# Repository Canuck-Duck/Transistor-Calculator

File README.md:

# Transistor-Calculator

V0.1 has many problems with the schematic and the PCB design. First, the schematic contains a mistake with both XOR segments. A wire is supposed to go from the right resistor under Q10 to 5V and from the right resistor under Q14 to 5V. Also, the design of the PCB is flawed because it is hard to hand-solder. While designing this PCB, I was too focused on saving space, which should not have been the case for the first version. The input and output holes were too small to fit any regular-size wire. All of these problems were fixed in V0.3.

V0.3 fixed all of the problems mentioned but still has some. For example, there are no mounting holes, so I had to drill holes in the PBC for the standoffs to stack them. Also, the 5V and GND will run through the standoffs for the following versions to facilitate disassembly. The carry pins will also be on the same side as the input since that's where it has to connect.

The 7-segment display module V1 translates an 8-bit binary number into an easier-to-read decimal number. This module can be connected anywhere in the calculator where the user wants to read the value of an 8-bit binary number. It uses two programmed EEPROMs to translate the 8-bit binary into 3 BCD, which are fed into 7-segment display drivers to convert the BCD for the 7-segment display (common anode).

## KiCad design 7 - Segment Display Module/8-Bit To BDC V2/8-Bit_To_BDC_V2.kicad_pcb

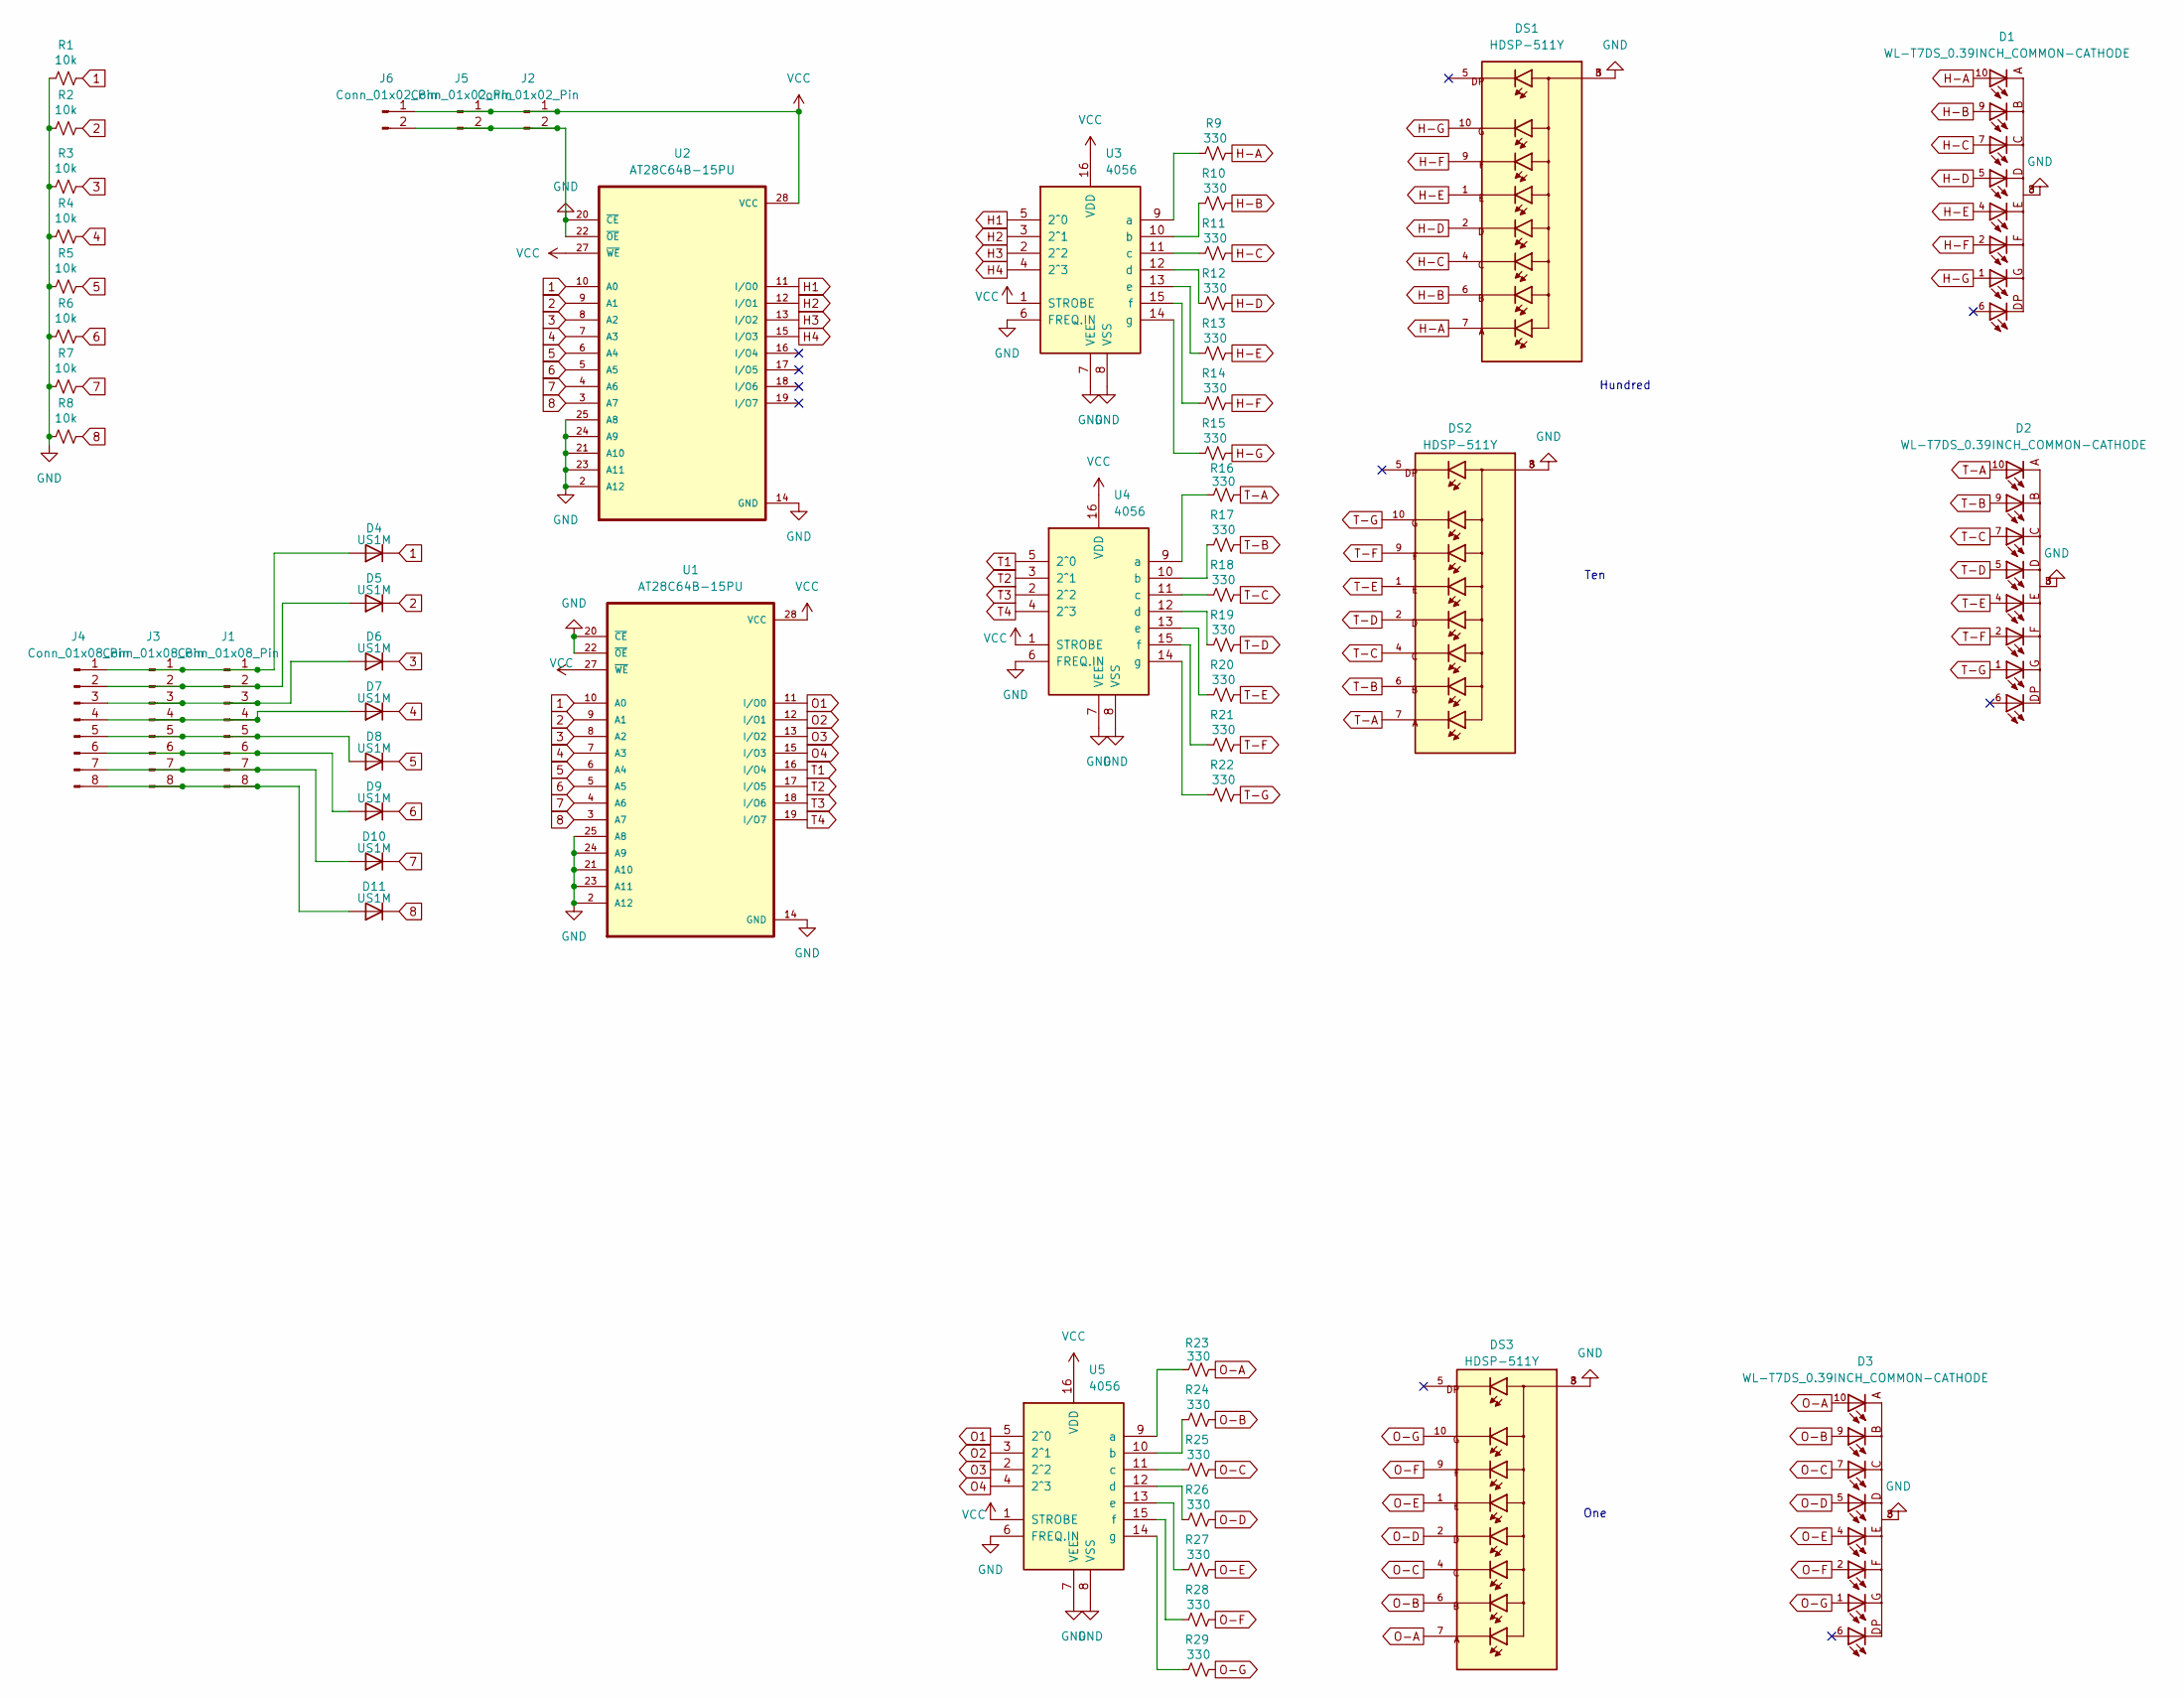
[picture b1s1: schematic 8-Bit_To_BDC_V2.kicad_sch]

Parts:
D1, D2, D3: WL-T7DS_0.39INCH_COMMON-CATHODE; WL-T7DS_0.39INCH
D4, D5, D6, D7, D8, D9, D10, D11: US1M; D_SOD-323_HandSoldering; LCSC C2128
DS1, DS2, DS3: HDSP-511Y; LED_HDSP-511Y; PARTREV April 12, 2021
J1, J3, J4: Conn_01x08_Pin; PinHeader_2x04_P2.54mm_Vertical
J2, J5, J6: Conn_01x02_Pin; PinHeader_1x02_P2.54mm_Vertical
R1, R2, R3, R4, R5, R6, R7, R8: 10k; C_0402_1005Metric_Pad0.74x0.62mm_HandSolder; LCSC C25744
R9, R10, R11, R12, R13, R14, R15, R16, R17, R18, R19, R20, R21, R22, R23, R24, R25, R26, R27, R28, R29: 330; R_0805_2012Metric_Pad1.20x1.40mm_HandSolder; LCSC C17630
U1, U2: AT28C64B-15PU; DIP1555W45P254L3733H482Q28; PARTREV B
U3, U4, U5: 4056; DIP794W45P254L1969H508Q16

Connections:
1: D4.1 (K), R1.2, U1.10 (A0), U2.10 (A0)
2: D5.1 (K), R2.2, U1.9 (A1), U2.9 (A1)
3: D6.1 (K), R3.2, U1.8 (A2), U2.8 (A2)
4: D7.1 (K), R4.2, U1.7 (A3), U2.7 (A3)
5: D8.1 (K), R5.2, U1.6 (A4), U2.6 (A4)
6: D9.1 (K), R6.2, U1.5 (A5), U2.5 (A5)
7: D10.1 (K), R7.2, U1.4 (A6), U2.4 (A6)
8: D11.1 (K), R8.2, U1.3 (A7), U2.3 (A7)
GND: D1.3, D1.8, D2.3, D2.8, D3.3, D3.8, DS1.3, DS1.8, DS2.3, DS2.8, DS3.3, DS3.8, J2.2, J5.2, J6.2, R1.1, R2.1, R3.1, R4.1, R5.1, R6.1, R7.1, R8.1, U1.2 (A12), U1.14 (GND), U1.20 (~CE), U1.21 (A10), U1.22 (~OE), U1.23 (A11), U1.24 (A9), U1.25 (A8), U2.2 (A12), U2.14 (GND), U2.20 (~CE), U2.21 (A10), U2.22 (~OE), U2.23 (A11), U2.24 (A9), U2.25 (A8), U3.6 (FREQ.IN), U3.7 (VEE), U3.8 (VSS), U4.6 (FREQ.IN), U4.7 (VEE), U4.8 (VSS), U5.6 (FREQ.IN), U5.7 (VEE), U5.8 (VSS)
H1: U2.11 (I/O0), U3.5 (2^0)
H2: U2.12 (I/O1), U3.3 (2^1)
H3: U2.13 (I/O2), U3.2 (2^2)
H4: U2.15 (I/O3), U3.4 (2^3)
H-A: D1.10, DS1.7, R9.2
H-B: D1.9, DS1.6, R10.2
H-C: D1.7, DS1.4, R11.2
H-D: D1.5, DS1.2, R12.2
H-E: D1.4, DS1.1, R13.2
H-F: D1.2, DS1.9, R14.2
H-G: D1.1, DS1.10, R15.2
unnamed: D4.2 (A), J1.1, J3.1, J4.1
unnamed: D5.2 (A), J1.2, J3.2, J4.2
unnamed: D6.2 (A), J1.3, J3.3, J4.3
unnamed: D7.2 (A), J1.4, J3.4, J4.4
unnamed: D8.2 (A), J1.5, J3.5, J4.5
unnamed: D9.2 (A), J1.6, J3.6, J4.6
unnamed: D10.2 (A), J1.7, J3.7, J4.7
unnamed: D11.2 (A), J1.8, J3.8, J4.8
unnamed: R9.1, U3.9 (a)
unnamed: R10.1, U3.10 (b)
unnamed: R11.1, U3.11 (c)
unnamed: R12.1, U3.12 (d)
unnamed: R13.1, U3.13 (e)
unnamed: R14.1, U3.15 (f)
unnamed: R15.1, U3.14 (g)
unnamed: R16.1, U4.9 (a)
unnamed: R17.1, U4.10 (b)
unnamed: R18.1, U4.11 (c)
unnamed: R19.1, U4.12 (d)
unnamed: R20.1, U4.13 (e)
unnamed: R21.1, U4.15 (f)
unnamed: R22.1, U4.14 (g)
unnamed: R23.1, U5.9 (a)
unnamed: R24.1, U5.10 (b)
unnamed: R25.1, U5.11 (c)
unnamed: R26.1, U5.12 (d)
unnamed: R27.1, U5.13 (e)
unnamed: R28.1, U5.15 (f)
unnamed: R29.1, U5.14 (g)
O1: U1.11 (I/O0), U5.5 (2^0)
O2: U1.12 (I/O1), U5.3 (2^1)
O3: U1.13 (I/O2), U5.2 (2^2)
O4: U1.15 (I/O3), U5.4 (2^3)
O-A: D3.10, DS3.7, R23.2
O-B: D3.9, DS3.6, R24.2
O-C: D3.7, DS3.4, R25.2
O-D: D3.5, DS3.2, R26.2
O-E: D3.4, DS3.1, R27.2
O-F: D3.2, DS3.9, R28.2
O-G: D3.1, DS3.10, R29.2
T1: U1.16 (I/O4), U4.5 (2^0)
T2: U1.17 (I/O5), U4.3 (2^1)
T3: U1.18 (I/O6), U4.2 (2^2)
T4: U1.19 (I/O7), U4.4 (2^3)
T-A: D2.10, DS2.7, R16.2
T-B: D2.9, DS2.6, R17.2
T-C: D2.7, DS2.4, R18.2
T-D: D2.5, DS2.2, R19.2
T-E: D2.4, DS2.1, R20.2
T-F: D2.2, DS2.9, R21.2
T-G: D2.1, DS2.10, R22.2
VCC: J2.1, J5.1, J6.1, U1.27 (~WE), U1.28 (VCC), U2.27 (~WE), U2.28 (VCC), U3.1 (STROBE), U3.16 (VDD), U4.1 (STROBE), U4.16 (VDD), U5.1 (STROBE), U5.16 (VDD)

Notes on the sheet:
Ten
One
Hundred

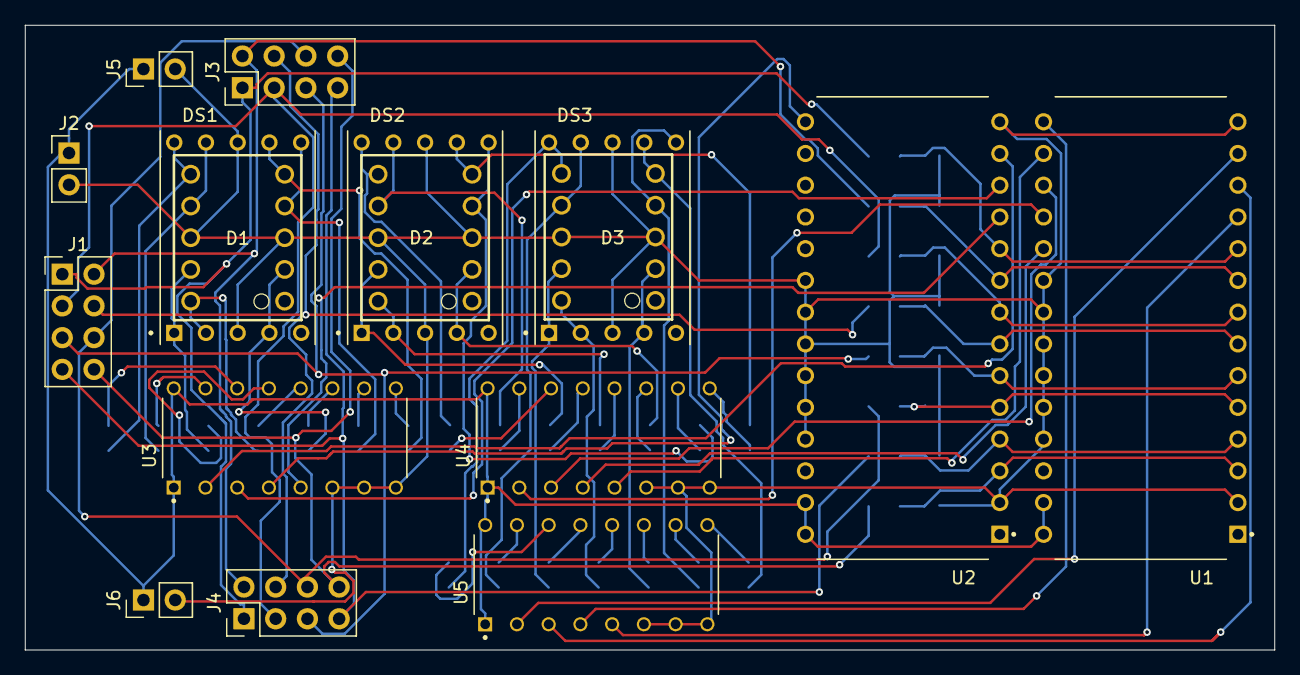
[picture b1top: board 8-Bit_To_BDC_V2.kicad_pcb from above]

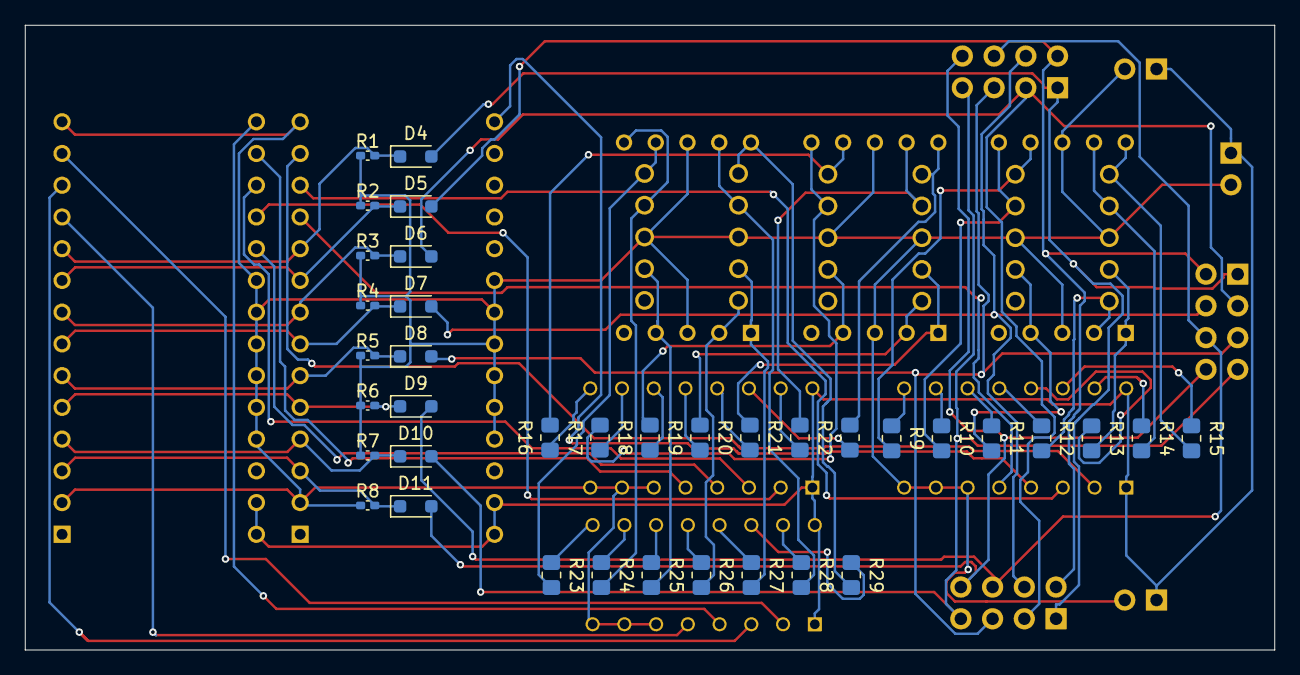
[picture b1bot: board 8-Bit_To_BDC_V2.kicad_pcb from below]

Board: 2 copper layers, 100.0 x 50.0 mm, 54 parts (37 on the bottom side), 72 nets.

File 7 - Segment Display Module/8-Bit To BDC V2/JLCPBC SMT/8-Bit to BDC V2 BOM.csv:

"null","Sourced","Placed","References","Value","Footprint","Quantity"
1,"","","R9, R10, R11, R12, R13, R14, R15, R16, R17, R18, R19, R20, R21, R23, R24, R25, R26, R27, R28, R29, R30",330,"R_0805_2012Metric_Pad1.20x1.40mm_HandSolder",21
2,"","","R1, R2, R3, R4, R5, R6, R7, R8","10k","C_0402_1005Metric_Pad0.74x0.62mm_HandSolder",8

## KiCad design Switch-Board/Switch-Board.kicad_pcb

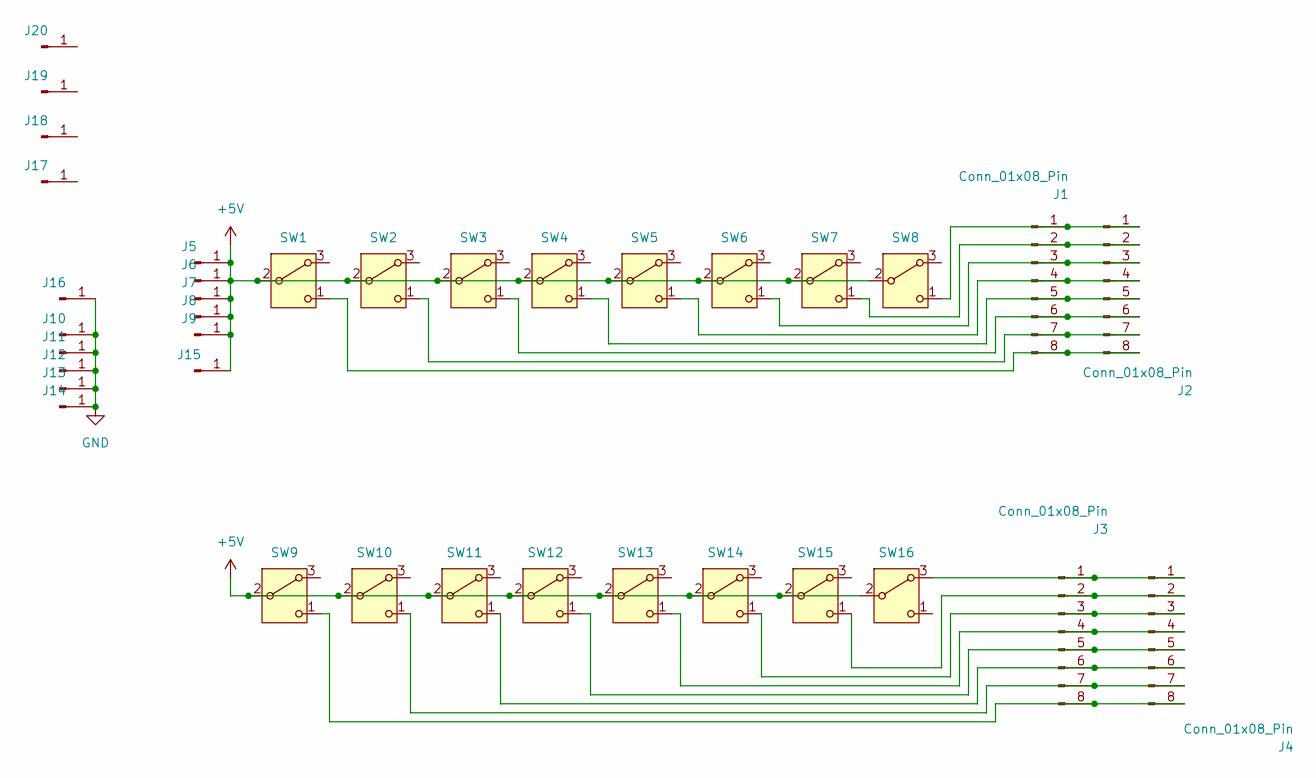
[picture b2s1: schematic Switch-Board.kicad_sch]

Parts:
J1, J3: Conn_01x08_Pin; PinSocket_2x04_P2.54mm_Vertical
J2, J4: Conn_01x08_Pin; PinHeader_1x08_P2.54mm_Vertical
J5, J6, J7, J8, J9: Conn_01x01_Pin; Pin_D1.0mm_L10.0mm_LooseFit
J10, J11, J12, J13, J14: Conn_01x01_Pin; Pin_D1.4mm_L8.5mm_W2.8mm_FlatFork
J15, J16: Conn_01x01_Pin; MountingHole_2.5mm_Pad
J17, J18, J19, J20: Conn_01x01_Pin; MountingHole_3.2mm_M3_DIN965_Pad
SW1, SW2, SW3, SW4, SW5, SW6, SW7, SW8, SW9, SW10, SW11, SW12, SW13, SW14, SW15, SW16: SW_Nidec_CAS-120A1; 5mm_Linear_Switch

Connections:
+5V: J5.1, J6.1, J7.1, J8.1, J9.1, J15.1, SW1.2 (B), SW2.2 (B), SW3.2 (B), SW4.2 (B), SW5.2 (B), SW6.2 (B), SW7.2 (B), SW8.2 (B), SW9.2 (B), SW10.2 (B), SW11.2 (B), SW12.2 (B), SW13.2 (B), SW14.2 (B), SW15.2 (B), SW16.2 (B)
GND: J10.1, J11.1, J12.1, J13.1, J14.1, J16.1
unnamed: J1.1, J2.1, SW8.1 (C)
unnamed: J1.2, J2.2, SW7.1 (C)
unnamed: J1.3, J2.3, SW6.1 (C)
unnamed: J1.4, J2.4, SW5.1 (C)
unnamed: J1.5, J2.5, SW4.1 (C)
unnamed: J1.6, J2.6, SW3.1 (C)
unnamed: J1.7, J2.7, SW2.1 (C)
unnamed: J1.8, J2.8, SW1.1 (C)
unnamed: J3.1, J4.1, SW16.3 (A)
unnamed: J3.2, J4.2, SW15.1 (C)
unnamed: J3.3, J4.3, SW14.1 (C)
unnamed: J3.4, J4.4, SW13.1 (C)
unnamed: J3.5, J4.5, SW12.1 (C)
unnamed: J3.6, J4.6, SW11.1 (C)
unnamed: J3.7, J4.7, SW10.1 (C)
unnamed: J3.8, J4.8, SW9.1 (C)

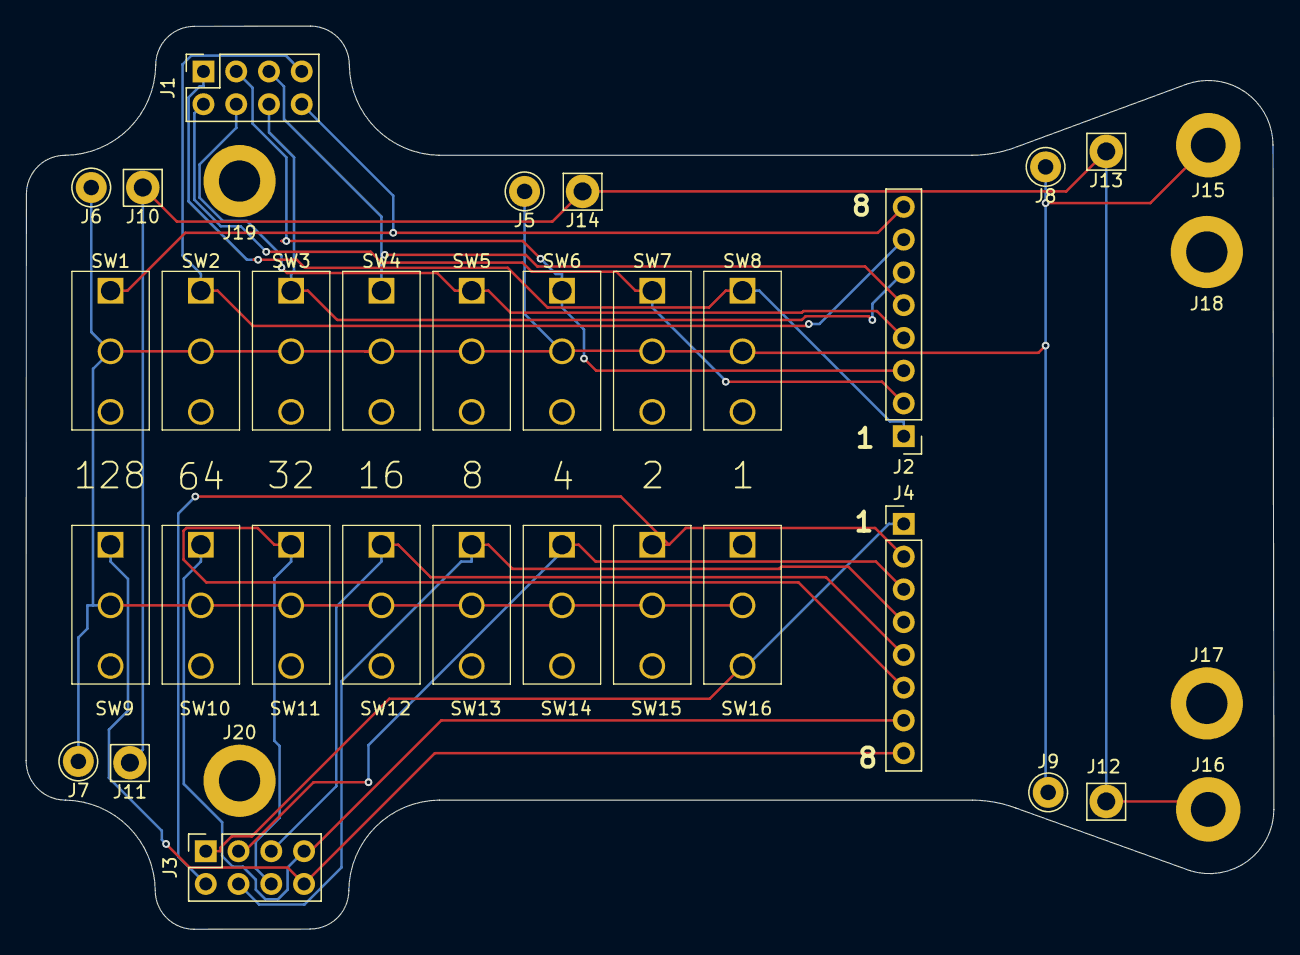
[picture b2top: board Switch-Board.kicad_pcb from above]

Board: 2 copper layers, 96.7 x 70.0 mm, 36 parts (0 on the bottom side), 18 nets.

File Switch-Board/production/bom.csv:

Designator,Footprint,Quantity,Value,LCSC Part #
"J1, J3",PinSocket_2x04_P2.54mm_Vertical,2,Conn_01x08_Pin,
"J10, J11, J12, J13, J14",Pin_D1.4mm_L8.5mm_W2.8mm_FlatFork,5,Conn_01x01_Pin,
"J15, J16",MountingHole_2.5mm_Pad,2,Conn_01x01_Pin,
"J17, J18, J19, J20",MountingHole_3.2mm_M3_DIN965_Pad,4,Conn_01x01_Pin,
"J2, J4",PinHeader_1x08_P2.54mm_Vertical,2,Conn_01x08_Pin,
"J5, J6, J7, J8, J9",Pin_D1.0mm_L10.0mm_LooseFit,5,Conn_01x01_Pin,
"SW1, SW10, SW11, SW12, SW13, SW14, SW15, SW16, SW2, SW3, SW4, SW5, SW6, SW7, SW8, SW9",5mm_Linear_Switch,16,SW_Nidec_CAS-120A1,

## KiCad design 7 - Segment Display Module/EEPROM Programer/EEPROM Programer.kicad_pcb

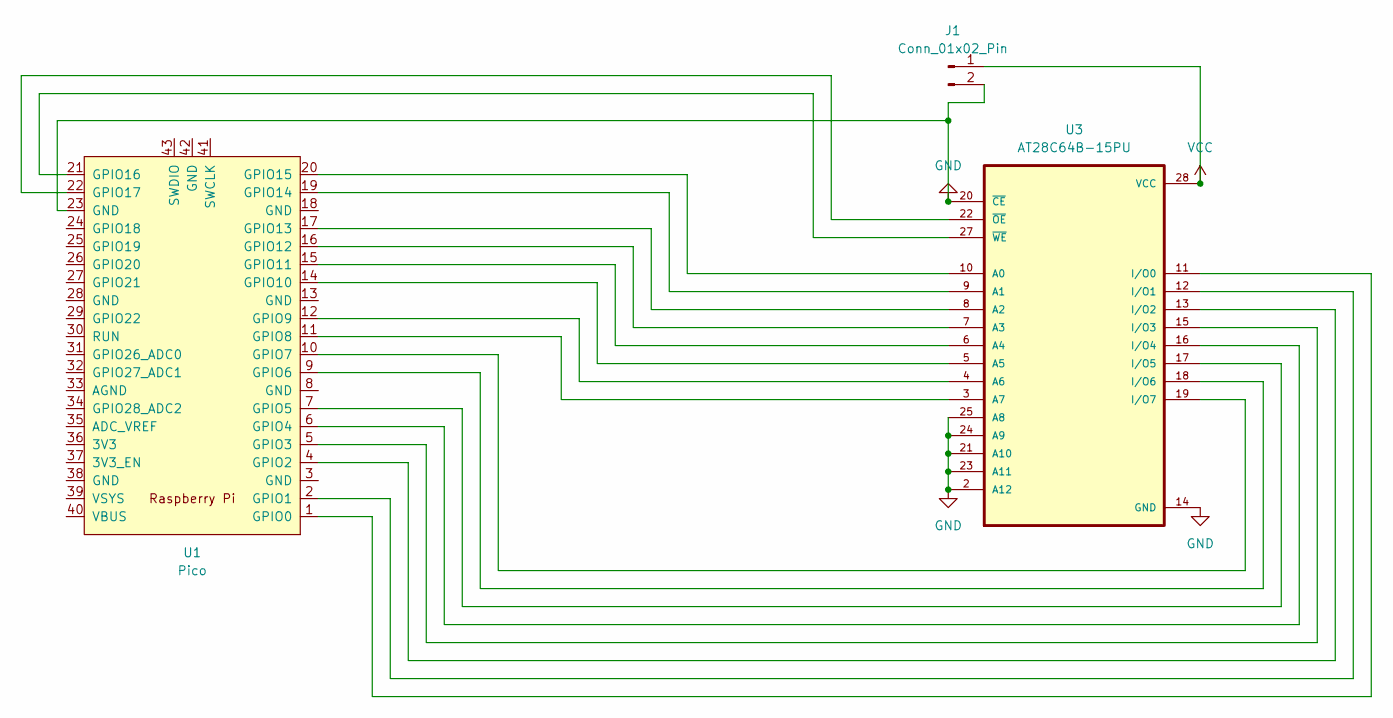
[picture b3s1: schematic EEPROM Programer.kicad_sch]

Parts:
J1: Conn_01x02_Pin; PinHeader_1x02_P2.54mm_Vertical
U1: Pico; RPi_Pico_SMD_TH
U3: AT28C64B-15PU; DIP1555W45P254L3733H482Q28; PARTREV B

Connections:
GND: J1.2, U1.23 (GND), U3.2 (A12), U3.14 (GND), U3.20 (~CE), U3.21 (A10), U3.23 (A11), U3.24 (A9), U3.25 (A8)
unnamed: U1.1 (GPIO0), U3.11 (I/O0)
unnamed: U1.2 (GPIO1), U3.12 (I/O1)
unnamed: U1.4 (GPIO2), U3.13 (I/O2)
unnamed: U1.5 (GPIO3), U3.15 (I/O3)
unnamed: U1.6 (GPIO4), U3.16 (I/O4)
unnamed: U1.7 (GPIO5), U3.17 (I/O5)
unnamed: U1.9 (GPIO6), U3.18 (I/O6)
unnamed: U1.10 (GPIO7), U3.19 (I/O7)
unnamed: U1.11 (GPIO8), U3.3 (A7)
unnamed: U1.12 (GPIO9), U3.4 (A6)
unnamed: U1.14 (GPIO10), U3.5 (A5)
unnamed: U1.15 (GPIO11), U3.6 (A4)
unnamed: U1.16 (GPIO12), U3.7 (A3)
unnamed: U1.17 (GPIO13), U3.8 (A2)
unnamed: U1.19 (GPIO14), U3.9 (A1)
unnamed: U1.20 (GPIO15), U3.10 (A0)
unnamed: U1.21 (GPIO16), U3.27 (~WE)
unnamed: U1.22 (GPIO17), U3.22 (~OE)
VCC: J1.1, U3.28 (VCC)

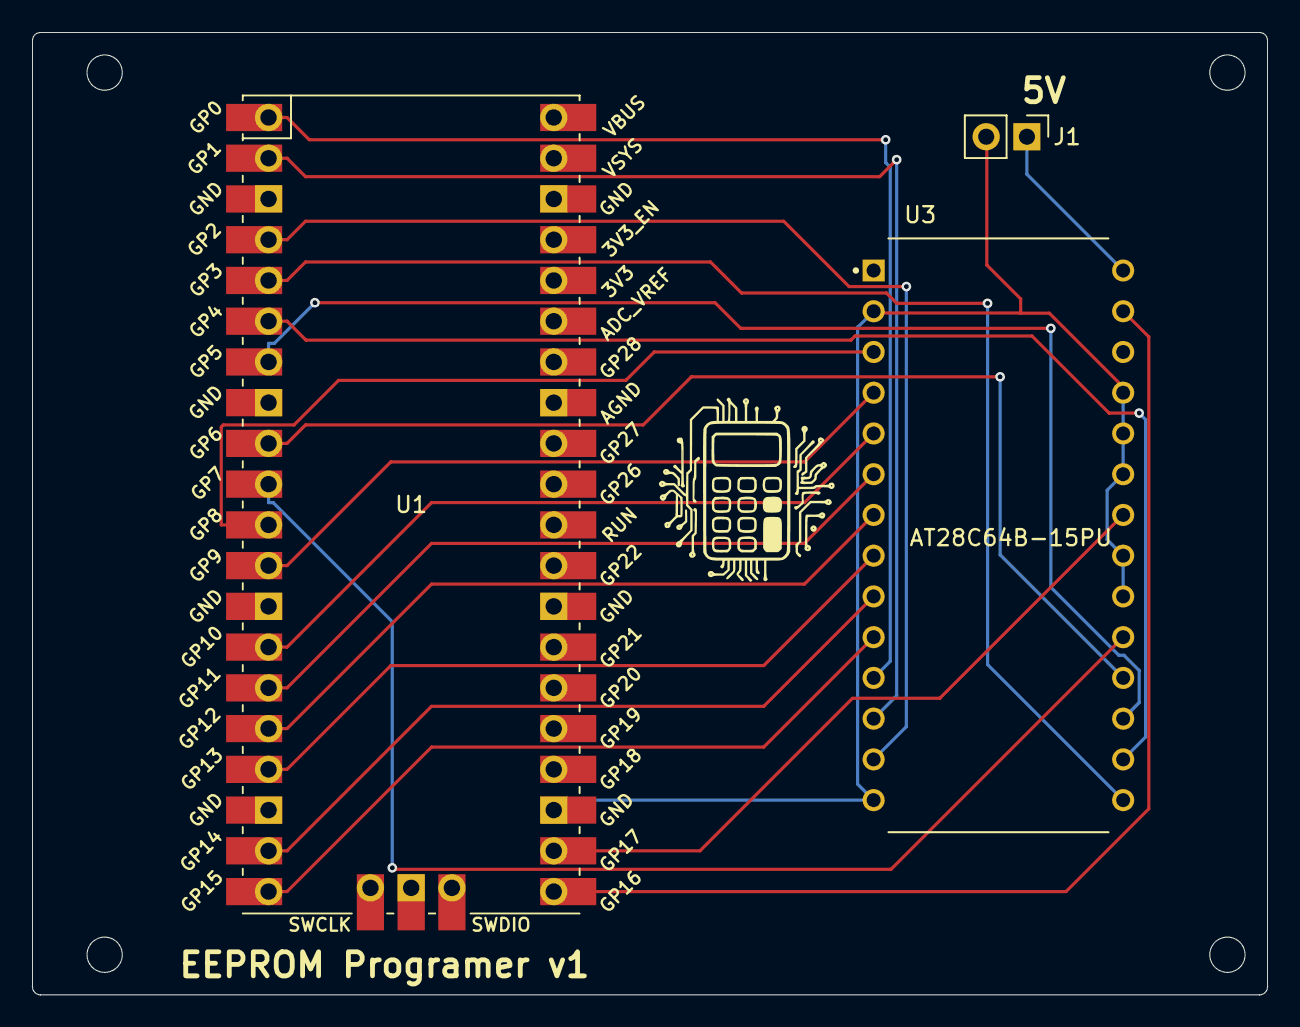
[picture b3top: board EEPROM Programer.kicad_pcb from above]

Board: 2 copper layers, 77.0 x 60.0 mm, 3 parts (0 on the bottom side), 20 nets.

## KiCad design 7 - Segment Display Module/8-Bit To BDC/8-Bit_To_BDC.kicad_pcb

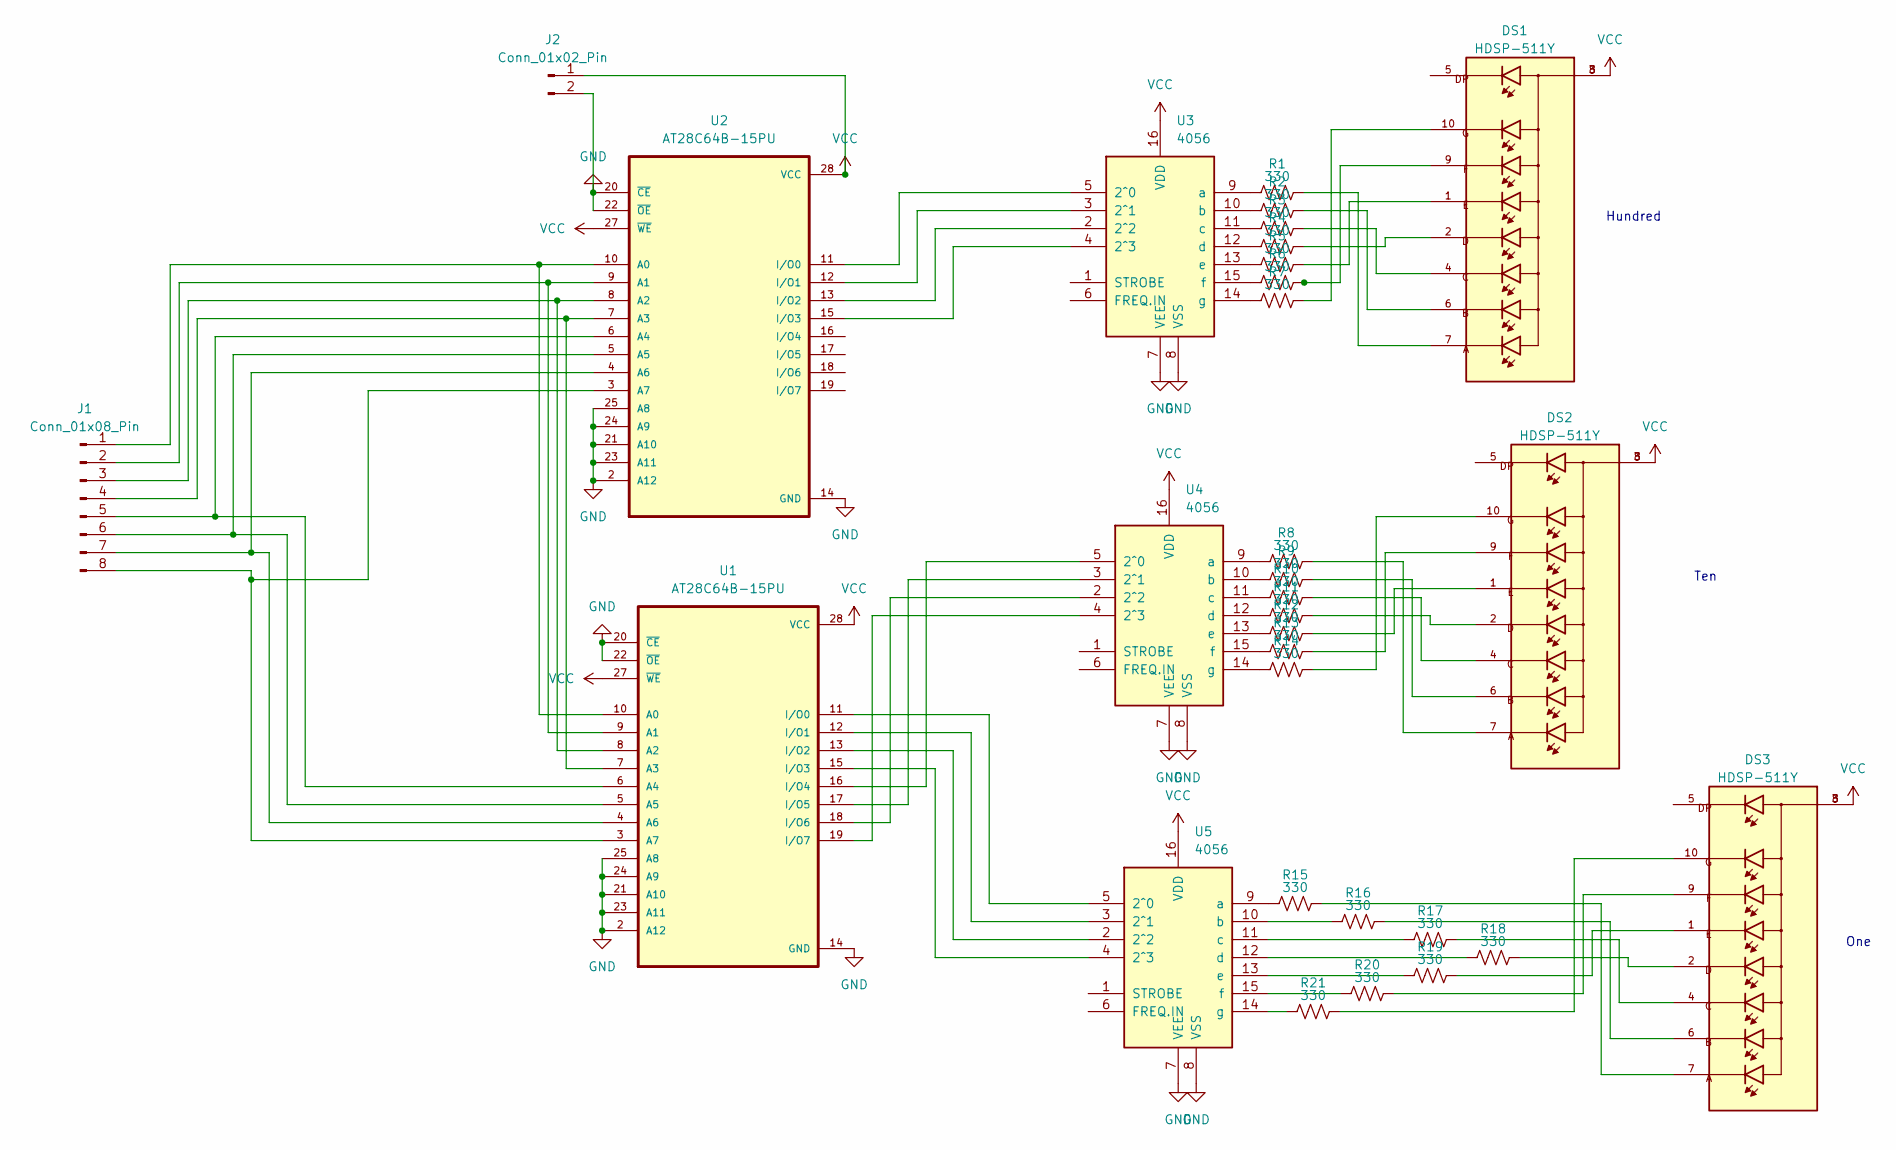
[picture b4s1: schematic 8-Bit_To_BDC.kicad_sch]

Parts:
DS1, DS2, DS3: HDSP-511Y; LED_HDSP-511Y; PARTREV April 12, 2021
J1: Conn_01x08_Pin; PinHeader_2x04_P2.54mm_Vertical
J2: Conn_01x02_Pin; PinHeader_1x02_P2.54mm_Vertical
R1, R2, R3, R4, R5, R6, R7, R8, R9, R10, R11, R12, R13, R14, R15, R16, R17, R18, R19, R20, R21: 330; R_Axial_DIN0204_L3.6mm_D1.6mm_P1.90mm_Vertical
U1, U2: AT28C64B-15PU; DIP1555W45P254L3733H482Q28; PARTREV B
U3, U4, U5: 4056; DIP794W45P254L1969H508Q16

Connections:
GND: J2.2, U1.2 (A12), U1.14 (GND), U1.20 (~CE), U1.21 (A10), U1.22 (~OE), U1.23 (A11), U1.24 (A9), U1.25 (A8), U2.2 (A12), U2.14 (GND), U2.20 (~CE), U2.21 (A10), U2.22 (~OE), U2.23 (A11), U2.24 (A9), U2.25 (A8), U3.7 (VEE), U3.8 (VSS), U4.7 (VEE), U4.8 (VSS), U5.7 (VEE), U5.8 (VSS)
unnamed: DS1.1, R5.2
unnamed: DS1.2, R4.2
unnamed: DS1.4, R3.2
unnamed: DS1.6, R2.2
unnamed: DS1.7, R1.2
unnamed: DS1.9, R6.2
unnamed: DS1.10, R7.2
unnamed: DS2.1, R12.2
unnamed: DS2.2, R11.2
unnamed: DS2.4, R10.2
unnamed: DS2.6, R9.2
unnamed: DS2.7, R8.2
unnamed: DS2.9, R13.2
unnamed: DS2.10, R14.2
unnamed: DS3.1, R19.2
unnamed: DS3.2, R18.2
unnamed: DS3.4, R17.2
unnamed: DS3.6, R16.2
unnamed: DS3.7, R15.2
unnamed: DS3.9, R20.2
unnamed: DS3.10, R21.2
unnamed: J1.1, U1.10 (A0), U2.10 (A0)
unnamed: J1.2, U1.9 (A1), U2.9 (A1)
unnamed: J1.3, U1.8 (A2), U2.8 (A2)
unnamed: J1.4, U1.7 (A3), U2.7 (A3)
unnamed: J1.5, U1.6 (A4), U2.6 (A4)
unnamed: J1.6, U1.5 (A5), U2.5 (A5)
unnamed: J1.7, U1.4 (A6), U2.4 (A6)
unnamed: J1.8, U1.3 (A7), U2.3 (A7)
unnamed: U1.11 (I/O0), U5.5 (2^0)
unnamed: U1.12 (I/O1), U5.3 (2^1)
unnamed: U1.13 (I/O2), U5.2 (2^2)
unnamed: U1.15 (I/O3), U5.4 (2^3)
unnamed: U1.16 (I/O4), U4.5 (2^0)
unnamed: U1.17 (I/O5), U4.3 (2^1)
unnamed: U1.18 (I/O6), U4.2 (2^2)
unnamed: U1.19 (I/O7), U4.4 (2^3)
unnamed: U2.11 (I/O0), U3.5 (2^0)
unnamed: U2.12 (I/O1), U3.3 (2^1)
unnamed: U2.13 (I/O2), U3.2 (2^2)
unnamed: U2.15 (I/O3), U3.4 (2^3)
unnamed: R1.1, U3.9 (a)
unnamed: R2.1, U3.10 (b)
unnamed: R3.1, U3.11 (c)
unnamed: R4.1, U3.12 (d)
unnamed: R5.1, U3.13 (e)
unnamed: R6.1, U3.15 (f)
unnamed: R7.1, U3.14 (g)
unnamed: R8.1, U4.9 (a)
unnamed: R9.1, U4.10 (b)
unnamed: R10.1, U4.11 (c)
unnamed: R11.1, U4.12 (d)
unnamed: R12.1, U4.13 (e)
unnamed: R13.1, U4.15 (f)
unnamed: R14.1, U4.14 (g)
unnamed: R15.1, U5.9 (a)
unnamed: R16.1, U5.10 (b)
unnamed: R17.1, U5.11 (c)
unnamed: R18.1, U5.12 (d)
unnamed: R19.1, U5.13 (e)
unnamed: R20.1, U5.15 (f)
unnamed: R21.1, U5.14 (g)
VCC: DS1.3, DS1.8, DS2.3, DS2.8, DS3.3, DS3.8, J2.1, U1.27 (~WE), U1.28 (VCC), U2.27 (~WE), U2.28 (VCC), U3.16 (VDD), U4.16 (VDD), U5.16 (VDD)

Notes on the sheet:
Ten
One
Hundred

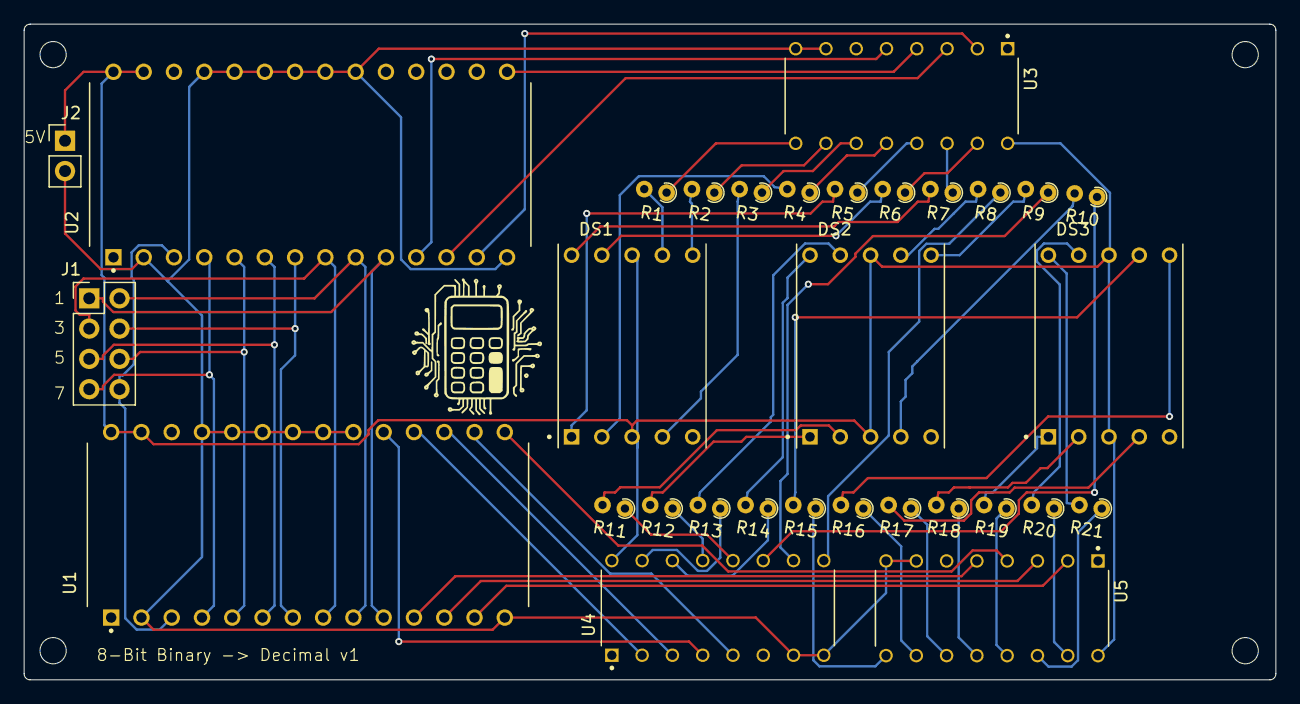
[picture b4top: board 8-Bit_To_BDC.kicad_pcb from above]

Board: 2 copper layers, 105.0 x 55.0 mm, 31 parts (0 on the bottom side), 64 nets.
